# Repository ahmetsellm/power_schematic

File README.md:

# 5V - 3.3V Voltage Regulator Board (LT1117-ADJ)

This repository contains the hardware files for a simple and stable 5V-to-3.3V step-down voltage regulator circuit, designed using KiCad.

## Hardware Details
The circuit is built around the LT1117-ADJ adjustable voltage regulator. The desired 3.3V output voltage is achieved using a voltage divider network formed by R1 (240Ω) and R2 (390Ω). Filter capacitors are used on both the input and output stages to suppress power line ripple and improve stability.

## Technical Specifications
* **Input:** 5V
* **Output:** 3.3V
* **Software Used:** KiCad EDA

## Bill of Materials (BOM)
| Reference | Component | Value | Footprint |
| :--- | :--- | :--- | :--- |
| U1 | Regulator | LT1117-ADJ | SOT-223-3 (SMD) |
| R1 | Resistor | 240Ω | Standard THT (Axial) |
| R2 | Resistor | 390Ω | Standard THT (Axial) |
| C1, C2 | Capacitor | 10uF | Polarized THT (Radial) |

## Screenshots

### Schematic

### PCB Layout

### 3D View

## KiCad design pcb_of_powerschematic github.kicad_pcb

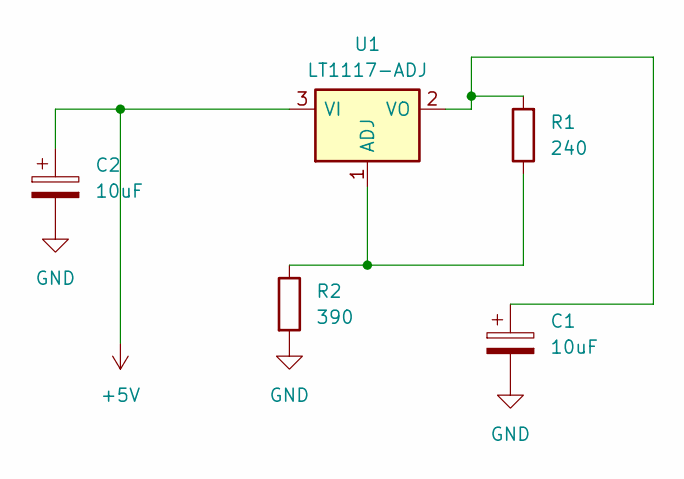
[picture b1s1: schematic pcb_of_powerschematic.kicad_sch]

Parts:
C1, C2: 10uF; CP_Radial_D4.0mm_P1.50mm
R1: 240; R_Axial_DIN0204_L3.6mm_D1.6mm_P5.08mm_Horizontal
R2: 390; R_Axial_DIN0204_L3.6mm_D1.6mm_P5.08mm_Horizontal
U1: LT1117-ADJ; SOT-223

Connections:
+5V: C2.1, U1.3 (VI)
GND: C1.2, C2.2, R2.2
unnamed: R1.1, R2.1, U1.1 (ADJ)
unnamed: C1.1, R1.2, U1.2 (VO)

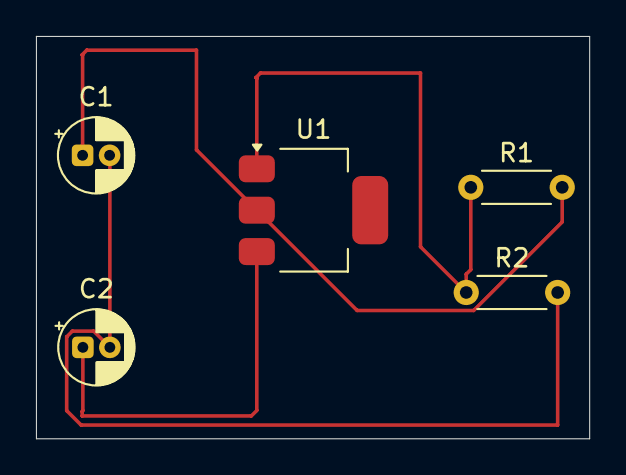
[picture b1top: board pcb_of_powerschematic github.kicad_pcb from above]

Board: 2 copper layers, 30.7 x 22.4 mm, 5 parts (0 on the bottom side), 4 nets.
